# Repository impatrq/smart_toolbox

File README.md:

<div align="center">

# [Smart Toolbox](https://smart-toolbox.vercel.app/)

&nbsp;

| Página web | Email | Instagram |
|------------|-------|-----------|
|[smart-toolbox.vercel.app](https://smart-toolbox.vercel.app/)|smart.toolbox@proton.me|[@smart.toolbox.2022](https://www.instagram.com/smart.toolbox.2022)|

&nbsp;

</div>

## ¿Qué es Smart Toolbox?

Smart Toolbox aborda la problemática de los _errores humanos_ en los entornos de trabajo con _herramientas_, que pueden producir _accidentes_ y/o _costos_ adicionales. Con la ayuda de diversas tecnologías creamos un sistema que permite tener un mayor control sobre las herramientas en un taller, reduciendo así el _riesgo de un siniestro_.

## ¿De dónde surgió la idea?

Este proyecto surgió como una variación de otro llamado _Tool Finder_. La principal función de este era la de encontrar, mediante un localizador, las herramientas de trabajo en el taller. A medida que ibamos progresando en el Tool Finder, se fueron descartando y transformando ideas, pero el objetivo de prevenir accidentes nunca cambió. Así surgió _Smart Toolbox_.

## ¿Cómo funciona?

Durante la jornada de trabajo, el operario _dispondrá de todas las tareas a realizar en el día en la aplicación móvil_. Estas serán cargadas a través de una página web.
Después de terminar la jornada de trabajo, el operario deberá guardar todas las herramientas en la caja y, de este modo, evitar el extravío de éstas. En el caso contrario, al cerrarse alguno de los cajones, el sistema _detectará que faltan herramientas_, avisándole de esto mediante un sonido. Los utensilios faltantes se podrán _visualizar en una aplicacion móvil_ vinculada a la caja y en una _interfaz gráfica_.

## Tecnologías utilizadas

### Aplicación móvil

- Ionic con React
- Typescript
- Bootstrap

### Interfaz gráfica

- Electron
- React
- Typescript
- Bootstrap

### Esquemáticos

- KiCad

### Página web

- Next.js
- Typescript
- TailwindCSS
- Bootstrap

### Base de datos

- Firebase Realtime Database

### Microcontrolador

- uPython

### Planos

- AutoCAD

## ¿Quiénes somos?

Somos un grupo de alumnos de E.E.S.T. N°7 "Taller Regional Quilmes" (IMPA).

### Esquivel, Agustín

--> 📧 esquivel.agustin04@gmail.com

### Herrera, Lucas

--> 📧 lucassherreraa2003@gmail.com

### Mariani, Ramiro

--> 📧 ramiromariani99@gmail.com

### Martínez Joaquín

--> 📧 joaquinosmartinez@gmail.com

### Torres, Federico

--> 📧 federicotorres233@protonmail.com

### Vanore, Miqueas

--> 📧 vnmiqueas@gmail.com

<div align="center">

</div>

## Logros

<div align="center">

### 🥇 Primer puesto en Prototipos II 🥇

</div>

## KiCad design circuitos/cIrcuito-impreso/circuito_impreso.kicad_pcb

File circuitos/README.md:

# Circuitos
Esta carpeta contiene los archivos de los esquemáticos y las placas de circuito impreso.

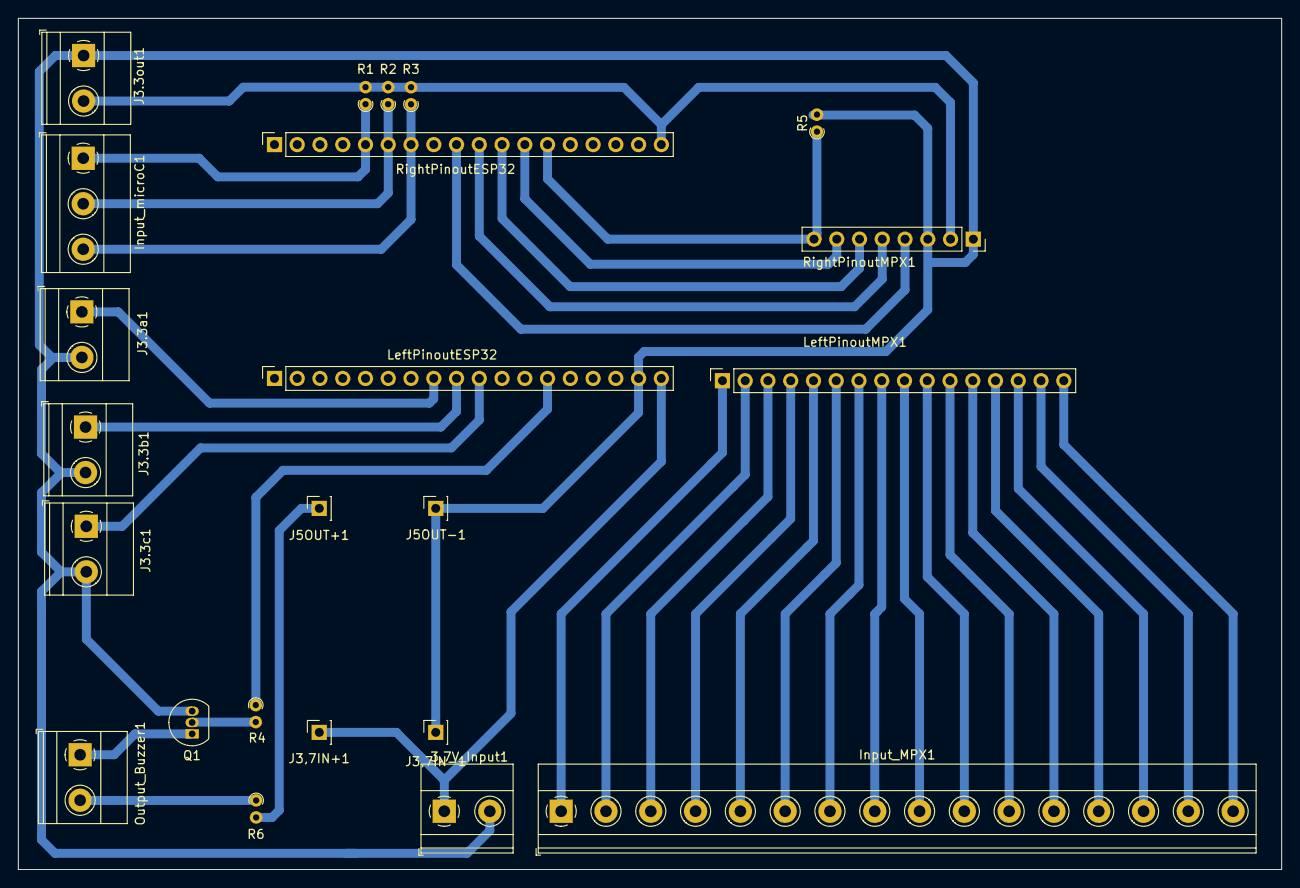
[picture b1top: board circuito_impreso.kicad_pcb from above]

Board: 2 copper layers, 141.0 x 95.0 mm, 23 parts (0 on the bottom side), 35 nets.

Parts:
3,7V_Input1: Screw_Terminal_01x02; TerminalBlock_Phoenix_MKDS-1,5-2-5.08_1x02_P5.08mm_Horizont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
Input_MPX1: Screw_Terminal_01x16; TerminalBlock_Phoenix_MKDS-1,5-16_1x16_P5.00mm_Horizontal
Input_microC1: Screw_Terminal_01x03; TerminalBlock_Phoenix_MKDS-1,5-3-5.08_1x03_P5.08mm_Horizont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
J3,7IN+1: Vin+; PinSocket_1x01_P2.54mm_Vertical
J3,7IN-1: Vin-; PinSocket_1x01_P2.54mm_Vertical
J3.3a1, J3.3b1, J3.3c1, J3.3out1: Screw_Terminal_01x02; TerminalBlock_Phoenix_MKDS-1,5-2-5.08_1x02_P5.08mm_Horizont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
J5OUT+1: Vout+; PinSocket_1x01_P2.54mm_Vertical
J5OUT-1: Vout-; PinSocket_1x01_P2.54mm_Vertical
LeftPinoutESP32: Conn_01x18_Female_Left; PinSocket_1x18_P2.54mm_Vertical
LeftPinoutMPX1: Conn_01x16_Female_Left; PinSocket_1x16_P2.54mm_Vertical
Output_Buzzer1: Alarma; TerminalBlock_Phoenix_MKDS-1,5-2-5.08_1x02_P5.08mm_Horizont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
Q1: BC548; TO-92_Inline
R1, R2, R3, R5: 4,7K; R_Axial_DIN0204_L3.6mm_D1.6mm_P1.90mm_Vertical
R4: 470; R_Axial_DIN0204_L3.6mm_D1.6mm_P1.90mm_Vertical
R6: 1K; R_Axial_DIN0204_L3.6mm_D1.6mm_P1.90mm_Vertical
RightPinoutESP32: Conn_01x18_Female_Right; PinSocket_1x18_P2.54mm_Vertical
RightPinoutMPX1: Conn_01x08_Female_Right; PinSocket_1x08_P2.54mm_Vertical

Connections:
3.3V: J3.3out1.2, R1.2, R2.2, R3.2, RightPinoutESP32.18, RightPinoutMPX1.2
3.7V: 3,7V_Input1.1, J3,7IN+1.1, LeftPinoutESP32.18
5V: J5OUT+1.1, R6.2
/C0: Input_MPX1.16, LeftPinoutMPX1.16
/C1: Input_MPX1.15, LeftPinoutMPX1.15
/C2: Input_MPX1.14, LeftPinoutMPX1.14
/C3: Input_MPX1.13, LeftPinoutMPX1.13
/C4: Input_MPX1.12, LeftPinoutMPX1.12
/C5: Input_MPX1.11, LeftPinoutMPX1.11
/C6: Input_MPX1.10, LeftPinoutMPX1.10
/C7: Input_MPX1.9, LeftPinoutMPX1.9
/C8: Input_MPX1.8, LeftPinoutMPX1.8
/C9: Input_MPX1.7, LeftPinoutMPX1.7
/C10: Input_MPX1.6, LeftPinoutMPX1.6
/C11: Input_MPX1.5, LeftPinoutMPX1.5
/C12: Input_MPX1.4, LeftPinoutMPX1.4
/C13: Input_MPX1.3, LeftPinoutMPX1.3
/C14: Input_MPX1.2, LeftPinoutMPX1.2
/C15: Input_MPX1.1, LeftPinoutMPX1.1
GND: 3,7V_Input1.2, J3,7IN-1.1, J3.3a1.2, J3.3b1.2, J3.3c1.2, J3.3out1.1, J5OUT-1.1, LeftPinoutESP32.17, Q1.3 (E), R5.2, RightPinoutMPX1.1, RightPinoutMPX1.3
GPIO2: RightPinoutESP32.12, RightPinoutMPX1.7
GPIO4: RightPinoutESP32.11, RightPinoutMPX1.6
GPIO13: LeftPinoutESP32.13, R4.1
GPIO15: R5.1, RightPinoutESP32.13, RightPinoutMPX1.8
GPIO16: RightPinoutESP32.10, RightPinoutMPX1.5
GPIO17: RightPinoutESP32.9, RightPinoutMPX1.4
GPIO18: Input_microC1.3, R3.1, RightPinoutESP32.7
GPIO19: Input_microC1.2, R2.1, RightPinoutESP32.6
GPIO21: Input_microC1.1, R1.1, RightPinoutESP32.5
GPIO25: J3.3a1.1, LeftPinoutESP32.8
GPIO26: J3.3b1.1, LeftPinoutESP32.9
GPIO27: J3.3c1.1, LeftPinoutESP32.10
unnamed: Output_Buzzer1.1, Q1.1 (C)
unnamed: Output_Buzzer1.2, R6.1
unnamed: Q1.2 (B), R4.2

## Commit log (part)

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2022-04-24 docs: añadir función de tareas
2022-04-27 docs: agregar funcionamiento del proyecto (#2)
    * docs: añadir función de tareas
    * docs: añadir función principal del sistema
2022-04-27 que_es_smart_toolbox (#3)
2022-06-08 feat: agregar interfaz grafica inicial
2022-06-08 chore: change typescript target to es6
2022-06-10 docs: arreglar el README
2022-06-10 docs: cambiar titulo
2022-06-10 docs: subir futuros posibles logros
2022-06-10 docs: agregar logo y titulo (#10)
    * docs: cambiar titulo
    * docs: agregar logo
2022-06-10 docs: agregar donde surge (#11)
2022-06-10 docs: cambiar logo
2022-06-12 docs: arreglar errores, cambiar logo de png a gif
2022-06-12 docs: utilizar logo .png por el momento
2022-06-14 docs: añadir pinout del esp32
2022-06-14 docs: mejorar readme y correjir errores
2022-06-14 docs: añadir datasheets (#15)
    * docs: añadir datasheet del esp32
    * docs: añadir pinout del esp32
    * docs: añadir datasheet del multiplexor
    * docs: añadir datasheet del lm7805
2022-06-14 docs: agregar datasheet del relay
2022-06-21 feat: agregar circuito KiCad (#18)
2022-06-24 feat: añadir programa inicial (#19)
2022-06-24 docs: agregar contacto y e-mails
2022-06-24 docs: achicar letra integrantes (#23)
    * docs: achicar letra de integrantes
    * docs: achicar letra de integrantes
2022-06-24 docs: rellenar información integrante (#24)
2022-06-29 feat: agregar aplicación móvil (#25)
2022-06-29 feat: cambiar tab2 a Herramientas
2022-06-29 hotfix: arreglar Tab3 label
2022-06-30 refactor: separar url de la db en partes
2022-07-06 feat: agregar clase Herramientas y constructor
2022-07-06 feat: añadir pagina inicial
2022-07-06 feat: usar bootstrap
2022-07-07 feat: añadir lista de herramientas (#28)
    * feat: agregar clase Herramientas y constructor
    * feat: crear un objeto por clase
    * feat: añadir advertencia
2022-07-07 docs: agregar datasheet de sensor optico (#30)
2022-07-07 docs: arreglar errores de ortografia en readme (#31)
2022-07-08 refactor: eliminar ExploreContainer
2022-07-08 refactor: agrupar rutas en sus carpetas
2022-07-09 docs: agregar lista herramientas diseño app
2022-07-09 docs: agregar lector qr diseño app
2022-07-09 docs: agregar lista de tareas diesño app
2022-07-10 feat: desarrollar pestaña de registro (#36)
2022-07-12 refactor: ordenar carpetas (#37)
2022-07-23 feat: agregar favicon
2022-07-23 feat: añadir video de fondo
2022-07-23 feat: añadir el componente de ayuda para navegar
2022-08-01 feat: añadir link de la pagina al readme
2022-08-03 style: cambiar color de fondo
2022-08-03 feat: añadir botones
2022-08-04 docs: reemplazar link en el titulo
2022-08-04 fix: arreglar seccion de contacto
2022-08-05 feat: crear componente de redes sociales
2022-08-05 feat: añadir iconos y sus respectivos links
2022-08-06 chore: actualizar links
2022-08-10 feat: hacer que se muestren las tareas correctamente
2022-08-13 feat: añadir I/O de los contactos magneticos
2022-08-13 chore: cambiar pines
2022-08-13 feat: añadir indentificacion de herramientas
2022-08-13 style: recortar logo
2022-08-13 style: cambiar algunos estilos
2022-08-14 feat: añadir tailwind a la pagina
2022-08-14 feat: desarrollar seccion de quienes somos
2022-08-14 fix: arreglar mapa en dispositivos moviles
2022-08-16 feat: crear-lista-en-pestaña-herramientas
2022-08-18 feat: mostrar valor del QR (#47)
2022-08-19 feat: agregar circuito actualizado
2022-08-21 feat: crear carpeta de fotos
2022-08-21 feat: crear funcion que lea el directorio pictures
2022-08-21 fix: solucionar error de estilos en el navbar
2022-08-21 fix: arreglar un problema en el mapa
2022-08-21 feat: cambiar el titulo de cada imagen
2022-08-24 refactor: remover datasheet desactualizado
2022-08-24 refactor: actualizar pinout esp32 (#50)
    * refactor: remover datasheet desactualizado
    * feat: añadir pinout esp32 actualizado
2022-08-27 feat: agregar titulo
2022-08-27 chore: usar un contacto por el momento
2022-08-27 feat: agregar puertos del multiplexor
2022-08-27 chore: agregar numero de caja
2022-08-27 feat: hacer un patch al detectar cambios
2022-08-28 feat: continuar codigo microcontrolador (#52)
    * feat: añadir I/O de los contactos magneticos
    * feat: empezar el codigo que verifica los contactos
    * chore: cambiar pines
    * chore: modificar constructor
    * feat: añadir indentificacion de herramientas
    * feat: añadir seleccion de contacto magnetico
2022-08-31 chore: cambiar a typescript
2022-08-31 feat: agregar cuentas de instagram
2022-08-31 fix: reemplazar los numeros de los archivos
2022-08-31 feat: cambiar paleta de colores
2022-08-31 fix: arreglar problemas entre typescript y css
2022-09-08 feat: actualizar codigo de android
2022-09-09 feat: añadir el archivo de word del anteproyecto
2022-09-09 docs: actualizar seccion de contacto
2022-09-09 fix: cambiar la seccion de integrantes
2022-09-09 docs: agregar powerpoint
2022-09-14 fix: arreglar css en la pagina de circuitos
2022-09-14 feat: añadir diagrama de flujo
2022-09-14 feat: añadir seccion de funcionamiento de la caja
2022-09-14 refactor: borrar dependencias sin usar
2022-09-14 feat: añadir bootstrap
2022-09-15 feat: crear pagina de inicio
2022-09-15 feat: crear seccion funcionamiento (#59)
    * fix: arreglar css en la pagina de circuitos
    * feat: añadir seccion de objetivo y funcionamiento
    * feat: añadir diagrama de flujo
    * feat: añadir seccion de funcionamiento de aplicacion movil
    * feat: añadir seccion de funcionamiento de interfaz grafica
    * feat: añadir seccion de funcionamiento de la caja
2022-09-15 refactor: cambiar logo (#60)
2022-09-16 feat: crear componente de Tareas
2022-09-17 feat: añadir bloque de input para añdir tareas
2022-09-17 feat: desarrollar página de agregar tareas (#62)
    * feat: crear componente de Tareas
    * feat: mostrar operario seleccionado de la db
    * feat: mostrar las tareas de cada operario
    * feat: añadir bloque de input para añdir tareas
    * feat: agregar funcionalidad de agregar y eliminar
2022-09-19 refactor: borrar esquematico descontinuado
2022-09-19 fix: arreglar tipos de typescript
2022-09-19 feat; agregar boton de usuario
2022-09-19 feat: agregar contexto de usuario
2022-09-20 feat: cambiar las tareas dependiendo del usuario
2022-09-20 chore: cambiar nombre de la app
2022-09-20 fix: arreglar declaracion de modulos
2022-09-21 feat: agregar mas fotos
2022-09-21 chore: cambiar foto de funcionamiento
2022-09-21 chore: cambiar foto de circuitos
2022-09-22 style: arreglar problemas de UI
2022-09-22 feat: compilar codigo android
2022-09-22 feat: subir apk aplicacion (#67)
    * feat: compilar codigo android
    * feat: subir apk
2022-09-23 feat: agregar tabla
2022-09-23 feat: crear columna de estado de caja
2022-09-23 feat: crear columna de operarios
2022-09-23 style: cambiar estilos
2022-09-23 feat: implementar seccion cajas interfaz (#68)
    * chore: agregar elemento a la ruta cajas
    * feat: agregar tabla
    * feat: agregar columnas
    * feat: crear columna de cajas
    * feat: crear columna de estado de caja
    * feat: crear columna de herramientas faltantes
2022-09-23 chore: cambiar URL en produccion
2022-09-23 chore: agregar autor
2022-09-23 fix: arreglar rutas de imagen para electron
2022-09-23 refactor: reordenar README
2022-09-23 refactor: eliminar datasheet del LM7805
2022-09-23 docs: agregar descripción de la interfaz gráfica
2022-09-23 docs: agregar descripción de circuitos
2022-09-24 fix: arreglar errores gramaticales
2022-09-24 fix: cambiar materiales utilizados
2022-09-24 feat: agregar linkedin personales
2022-09-24 feat: agregar instagram del proyecto
2022-09-24 docs: arreglar error de tipeo en readme
2022-09-24 Docs: arreglar errores de tipeo (#72)
    * docs: arreglar error de tipeo en readme
    * docs: arreglar error de redaccion en readme
2022-09-29 refactor: cambiar a OOP
2022-09-29 refactor: eliminar codigo innecesario
2022-09-30 feat: crear primer prototipo de codigo de uC (#73)
    * feat: crear programa de testeo de uC
    * feat: agregar programa hardcodeado de deteccion
    * refactor: cambiar a OOP
    * feat: agregar alarma
    * refactor: eliminar codigo innecesario
    * docs: agregar comentarios
2022-10-01 feat: añadir métodos REST
2022-10-01 feat: subir a la base de datos las herramientas
2022-10-01 feat: make the uC wait until the store signal
2022-10-01 refactor: aplicar formato
2022-10-03 fix: ajustar tamaño de las cards
2022-10-03 feat: añadir mas fotos
2022-10-04 chore: borrar pptx desactualizado
2022-10-05 refactor: organizar componentes en carpetas
2022-10-05 feat: agregar modal de cajas
2022-10-05 feat: agregar aplicacion de escritorio version 2
2022-10-05 refactor: eliminar un IonHeader sin usar
2022-10-05 refactor: refactorizar app movil (#79)
    * refactor: reorganizar imports
    * refactor: eliminar un IonHeader sin usar
    * feat: crear componente HeaderBar
2022-10-11 feat: agregar circuito finalizado e imagenes
2022-10-11 feat: agregar circuito impreso e imagenes (#81)
2022-10-11 docs: añadir datasheet del transistor bc337 (#82)
2022-10-14 feat: esconder herramientas vacías
2022-10-14 feat: agregar apk
2022-10-17 feat: cambiar de scroll horizontal a vertical
2022-10-17 feat: agregar foto a circuitos
2022-10-18 chore: eliminar fondo negro en movil
2022-10-21 chore: arreglar README
2022-10-21 feat: eliminar datasheet del rele
2022-10-21 feat: modificar datasheets (#86)
    * feat: eliminar datasheet del rele
    * feat: añadir datasheet step up
2022-11-01 docs: agregar cortes de linea
2022-11-01 chore: cambiar seccion de nosotros
2022-11-01 chore: cambiar email
2022-11-02 feat: añadir imagen de Smart Toolbox en ONIET
2022-11-02 refactor: eliminar archivos innecesarios (#88)
    * refactor: eliminar gitignore
    * refactor: eliminar prototipo ideal
2022-11-05 feat: añadir codigo actualizado con contactos magneticos
2022-11-05 refactor: eliminar print functions
2022-11-10 feat: agregar foto de ejemplo de la base de datos
2022-11-10 feat: agregar base de datos (#91)
    * feat: agregar foto de ejemplo de la base de datos
    * feat: agregar esquema JSON
2022-11-12 chore: cambiar licencia (#92)
2022-11-19 chore: añadir presentacion nueva
2022-11-19 chore: cambiar certificado ONIET
2022-11-23 docs: añadir foto del grupo
2022-11-23 docs: agregar README.md a base de datos
2022-11-25 docs: agregar carpeta de campo
2022-11-25 docs: subir banner
2022-11-28 feat: añadir carpeta tecnica (#98)
